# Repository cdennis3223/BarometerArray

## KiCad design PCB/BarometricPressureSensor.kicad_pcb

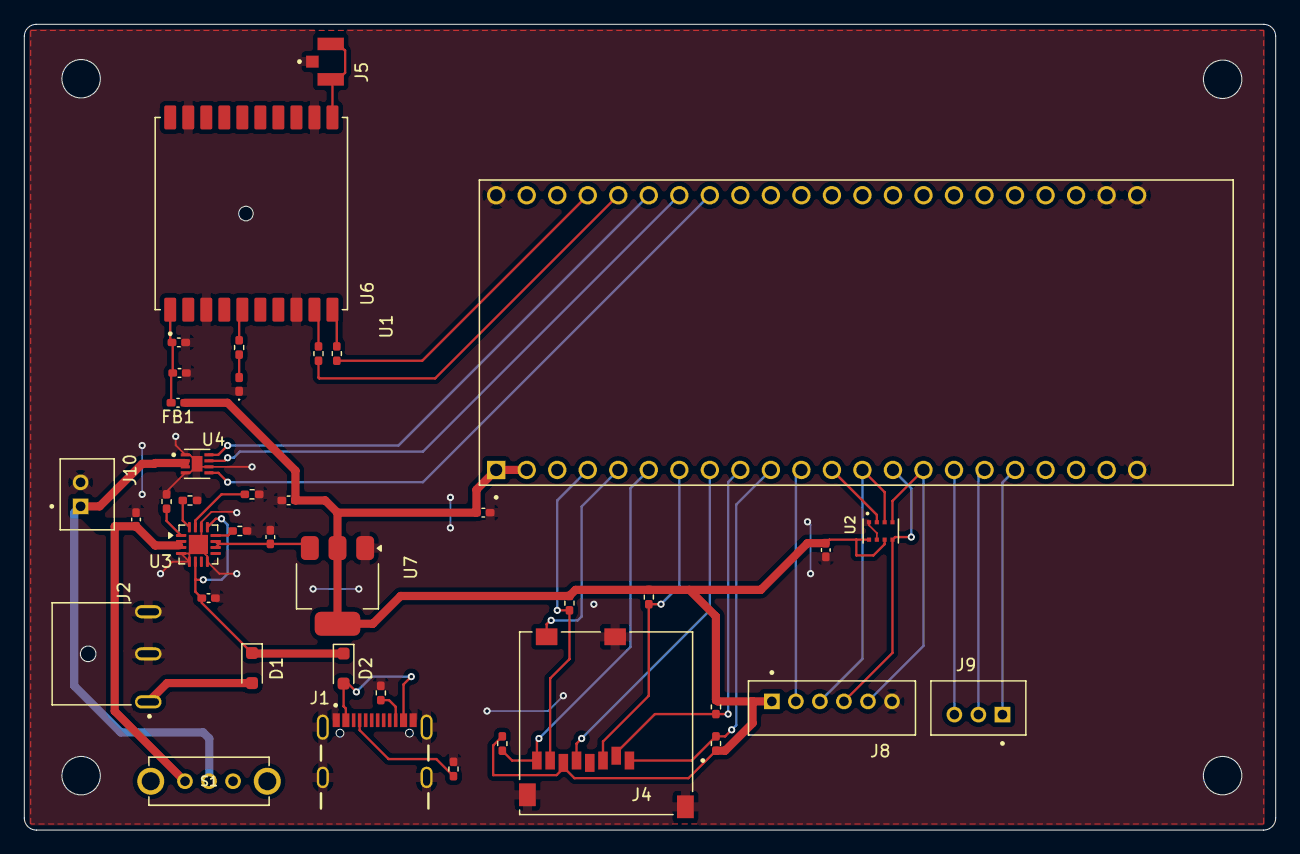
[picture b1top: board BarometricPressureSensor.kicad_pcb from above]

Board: 2 copper layers, 104.1 x 67.1 mm, 40 parts (0 on the bottom side), 39 nets.

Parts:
C1, C3: 100nF; C_0402_1005Metric_Pad0.74x0.62mm_HandSolder
C2, C8: 10uF; C_0402_1005Metric_Pad0.74x0.62mm_HandSolder
C4, C7: 1uF; C_0402_1005Metric_Pad0.74x0.62mm_HandSolder
C5: 0.1uF; C_0402_1005Metric_Pad0.74x0.62mm_HandSolder
C6: 4.7uF; C_0402_1005Metric_Pad0.74x0.62mm_HandSolder
D1, D2: D_Schottky; D_SOD-323_HandSoldering
D3: LED; LED_0402_1005Metric_Pad0.77x0.64mm_HandSolder
FB1: FerriteBead_Small; L_0402_1005Metric_Pad0.77x0.64mm_HandSolder
J1: USB4105-GF-A; GCT_USB4105-GF-A
J2: 54-00125; TENSILITY_54-00125
J4: GTFP08441BEU; AMPHENOL_GTFP08441BEU
J5: 2337019-1; TE_2337019-1
J8: B6B-PH-K-S; JST_B6B-PH-K-S
J9: B3B-PH-K-S; JST_B3B-PH-K-S
J10: B2B-PH-K-S; JST_B2B-PH-K-S
R1, R2: 5.1k; R_0402_1005Metric_Pad0.72x0.64mm_HandSolder
R3, R7, R8, R9, R10, R11: 10k; R_0402_1005Metric_Pad0.72x0.64mm_HandSolder
R4, R6: 3k; R_0402_1005Metric_Pad0.72x0.64mm_HandSolder
R5: 300; R_0402_1005Metric_Pad0.72x0.64mm_HandSolder
R12, R13, R14: 470; R_0402_1005Metric_Pad0.72x0.64mm_HandSolder
S1: EG1213; SW_EG1213
U1: ESP32-S3-DEVKITC-1-N16R8V; XCVR_ESP32-S3-DEVKITC-1-N16R8V
U2: DPS368XTSA1; XDCR_DPS368XTSA1
U3: BQ24074RGT; VQFN-16-1EP_3x3mm_P0.5mm_EP1.6x1.6mm
U4: MAX17048G_T10; SON50P200X200X80-9N
U6: CD-PA1616D; XCVR_CD-PA1616D
U7: LD1117S33TR_SOT223; SOT-223-3_TabPin2

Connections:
+3V3: C2.1, C3.2, C8.1, FB1.1, J4.6 (VSS), J8.1, R7.1, R8.1, R9.1, R10.2, R11.2, U1.J1_1 (3V3), U1.J1_2 (3V3), U2.6 (VDDIO), U2.8 (VDD), U7.2 (VO)
+BATT: C6.1, J10.1, S1.1, S1.2, U3.2 (BAT), U3.3 (BAT), U4.2 (CELL), U4.3 (VDD)
/CMD: J4.3 (CMD), R7.2, U1.J1_7 (GPIO7)
/CS1: U1.J1_12 (GPIO8), U2.2 (CSB)
/CS2: J8.2, U1.J1_11 (GPIO18)
/D0: J4.7 (DAT0), R11.1, U1.J1_4 (GPIO4)
/D1: J4.8 (DAT1), R10.1, U1.J1_6 (GPIO6)
/D2: J4.1 (DAT2), R8.2, U1.J1_10 (GPIO17)
/D3: J4.2 (CD/DAT3), R9.2, U1.J1_9 (GPIO16)
/DPSCLK: J8.5, U1.J1_15 (GPIO9), U2.4 (SCK)
/DPSMISO: J8.4, U1.J1_14 (GPIO46), U2.5 (SDO)
/DPSMOSI: J8.3, U1.J1_13 (GPIO3), U2.3 (SDI)
/GPSRX: R13.1, U1.J3_5 (GPIO2)
/GPSTX: R14.1, U1.J3_4 (GPIO1)
/IN: C7.1, D1.1 (K), D2.1 (K), U3.6 (EN1), U3.13 (IN)
/MAXALRT: U1.J3_8 (MTDO/GPIO40), U4.5 (~ALERT)
/MAXSCL: U1.J3_7 (MTDI/GPIO41), U4.7 (SCL)
/MAXSDA: U1.J3_6 (MTMS/GPIO42), U4.8 (SDA)
/OLEDBUT: J9.3, U1.J1_16 (GPIO10)
/OLEDSCL: J9.2, U1.J1_17 (GPIO11)
/OLEDSDA: J9.1, U1.J1_18 (GPIO12)
/SDCLK: J4.5 (CLK), U1.J1_8 (GPIO15)
/SDDET: J4.CD_PIN, U1.J1_5 (GPIO5)
GND: C1.2, C2.2, C3.1, C4.2, C5.2, C6.2, C7.2, C8.2, D3.1 (K), J1.A1_B12 (GND), J1.B1_A12 (GND__1), J1.SH1 (SHELL_GND), J1.SH2 (SHELL_GND__1), J1.SH3 (SHELL_GND__2), J1.SH4 (SHELL_GND__3), J2.B, J2.C, J4.G1 (SHIELD_GND), J4.G2 (SHIELD_GND__1), J4.G3 (SHIELD_GND__2), J5.1, J8.6, J10.2, R1.2, R2.2, R3.2, R4.1, R5.1, R6.1, U1.J1_22 (GND), U1.J3_1 (GND), U1.J3_21 (GND), U1.J3_22 (GND), U2.1 (GND), U2.7 (GND), U3.4 (~CE), U3.5 (EN2), U3.8 (VSS), U3.14 (TMR), U3.17 (VSS), U4.1 (CTG), U4.4 (GND), U4.6 (QSTRT), U4.9 (EP), U6.3 (GND), U6.8 (GND), U6.12 (GND), U6.19 (GND), U7.1 (GND)
unnamed: D1.2 (A), J2.A
unnamed: D2.2 (A), J1.A4_B9 (VBUS), J1.B4_A9 (VBUS__1)
unnamed: D3.2 (A), R12.2
unnamed: J1.A5 (CC1), R1.1
unnamed: J1.B5 (CC2), R2.1
unnamed: R6.2, U3.12 (ILIM)
unnamed: R4.2, U3.16 (ISET)
unnamed: R5.2, U3.15 (ITERM)
unnamed: R3.1, U3.1 (TS)
unnamed: R12.1, U6.5 (3D-FIX)
unnamed: J5.G1, J5.G2, U6.11 (EX_ANT)
unnamed: R14.2, U6.10 (RX)
unnamed: R13.2, U6.9 (TX)
unnamed: C4.1, C5.1, FB1.2, U6.1 (VCC)
unnamed: C1.1, U3.10 (OUT), U3.11 (OUT), U7.3 (VI)

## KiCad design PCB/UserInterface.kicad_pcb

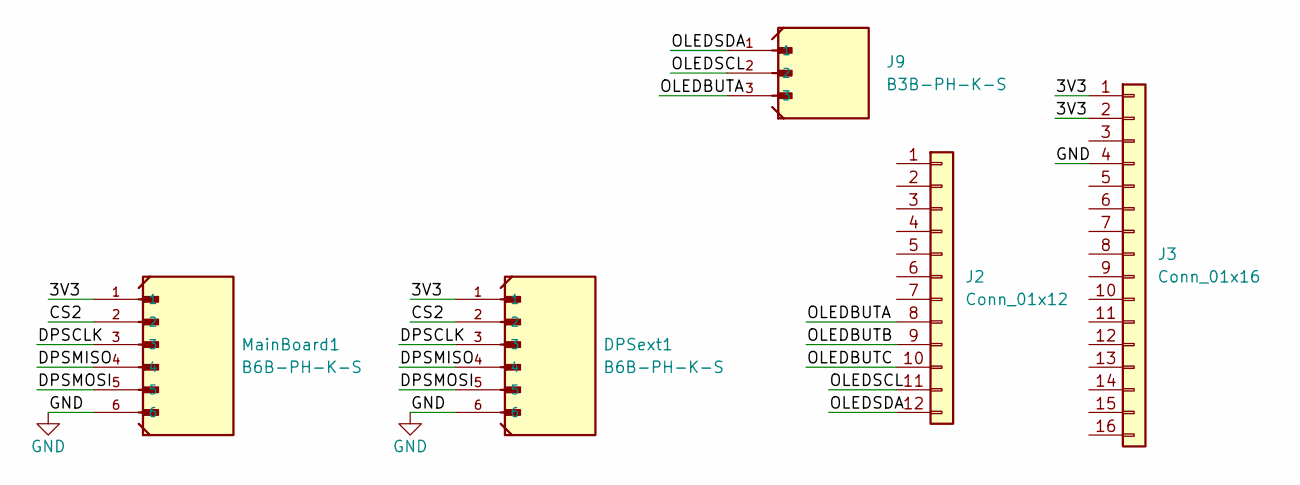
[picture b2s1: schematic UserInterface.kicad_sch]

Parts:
DPSext1: B6B-PH-K-S; JST_B6B-PH-K-S
J2: Conn_01x12; PinSocket_1x12_P2.54mm_Vertical
J3: Conn_01x16; PinSocket_1x16_P2.54mm_Vertical
J9: B3B-PH-K-S; JST_B3B-PH-K-S
MainBoard1: B6B-PH-K-S; JST_B6B-PH-K-S

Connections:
/3V3: DPSext1.1, J3.1, J3.2, MainBoard1.1
/CS2: DPSext1.2, MainBoard1.2
/DPSCLK: DPSext1.3, MainBoard1.3
/DPSMISO: DPSext1.4, MainBoard1.4
/DPSMOSI: DPSext1.5, MainBoard1.5
/OLEDBUTA: J2.8, J9.3
/OLEDBUTB: J2.9
/OLEDBUTC: J2.10
/OLEDSCL: J2.11, J9.2
/OLEDSDA: J2.12, J9.1
GND: DPSext1.6, J3.4, MainBoard1.6

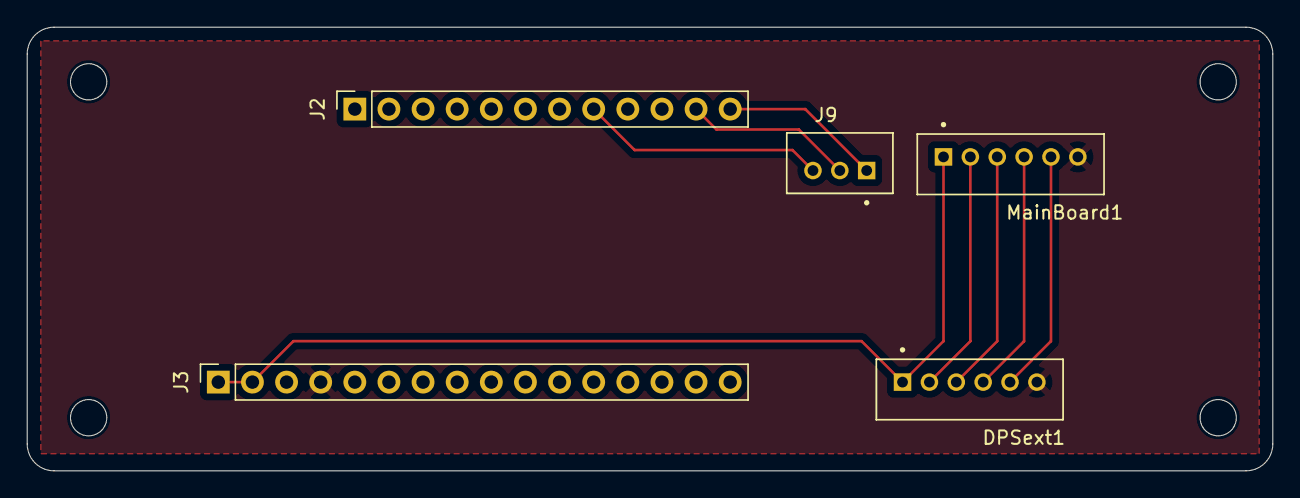
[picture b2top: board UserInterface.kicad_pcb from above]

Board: 2 copper layers, 92.7 x 33.0 mm, 5 parts (0 on the bottom side), 9 nets.

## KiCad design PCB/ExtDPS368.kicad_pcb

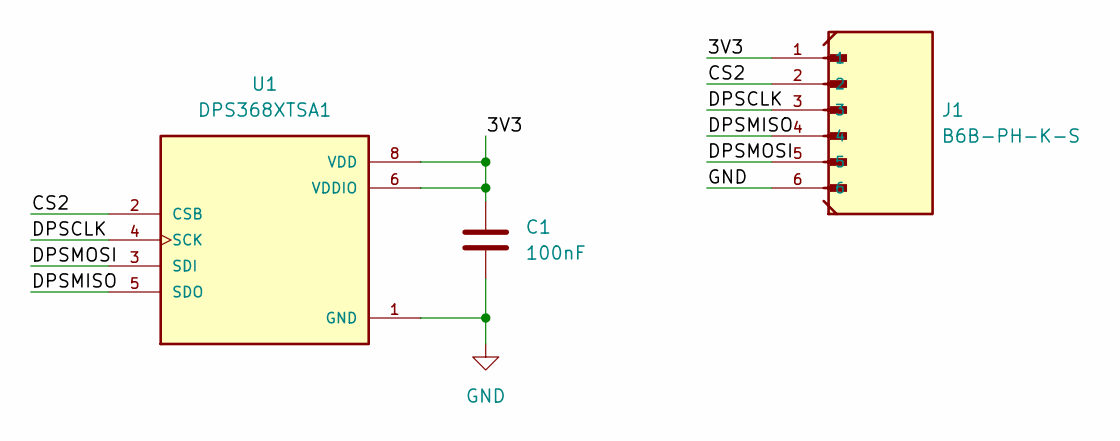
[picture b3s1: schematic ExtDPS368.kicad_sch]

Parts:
C1: 100nF; C_0402_1005Metric_Pad0.74x0.62mm_HandSolder
J1: B6B-PH-K-S; JST_B6B-PH-K-S
U1: DPS368XTSA1; XDCR_DPS368XTSA1

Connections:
/3V3: C1.1, J1.1, U1.6 (VDDIO), U1.8 (VDD)
/CS2: J1.2, U1.2 (CSB)
/DPSCLK: J1.3, U1.4 (SCK)
/DPSMISO: J1.4, U1.5 (SDO)
/DPSMOSI: J1.5, U1.3 (SDI)
GND: C1.2, J1.6, U1.1 (GND), U1.7 (GND)

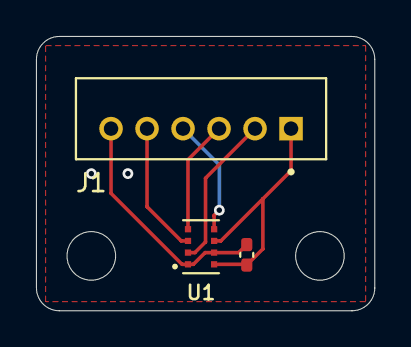
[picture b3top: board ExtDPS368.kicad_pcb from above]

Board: 2 copper layers, 18.8 x 15.2 mm, 3 parts (0 on the bottom side), 6 nets.

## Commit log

2026-02-02 attempting to push to Carl's repo
2026-02-02 Microcontroller communicates with GPS module.
2026-02-02 trying to push to Carls repo
2026-02-02 another attempt
2026-02-02 Hoping this goes through
2026-02-03 Moved files around
2026-02-03 Moved GPS code to separte source and header file. Code works
2026-02-04 My First Commit
2026-02-05 I think I have established communication with the pressure sensor. However I am just printing a serial number currently.
2026-02-09 The MISO and SCLK lines are working however the SDO of the DPS is not working. There seems to be a vague square wave but it is small and malformed
2026-02-09 this is old potentially working code
2026-02-11 Added Coefficient function and updated main to obtain them
2026-02-11 Fixed the Coefficient Values
2026-02-11 Updated Coefficients and corrected Temperature and pressure equations
2026-02-11 Currently Trying to debug Scaling issue with pressure and temperature output
2026-02-13 Working DPS Sensor, still finalizing initialization
2026-02-16 working Code for DPS Sensor, All initialization in the DPS.c file.
2026-02-18 Initial portions of SD.c and SD.h to start writing to the SD Card, Not tested Yet.
2026-02-27 clean code that prints horizontal!
2026-03-02 worked on encapsulating functions from main to DPS.c pressure sensor modules, good progress, code is cleaner still needs some work
2026-03-03 better organized the code for the pressure sensor module
2026-03-06 Reorganized repo: firmware files moved into firmware folder and added a PCB and mechanical folder
2026-03-06 new folders were not added to remote because they were empth, I fixed the issue by adding .gitkeep files within PCB and mechanical folders
2026-03-09 Working SD card code and untested BatMGMT code
2026-03-09 Fixing File errors
2026-03-11 Add files via upload
    Updated the switch we are using for the PCB. Will need to order these switches on our own.
2026-03-12 Add files via upload
    Updated Sizing on User Interface
2026-03-21 created a new collate module that implements a ring buffer to store timestamped measurements from the DPS368 pressure sensor before pushing it to the SD card. There is a task that runs in collate.c t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
2026-03-23 Updated BatMGMT.c and .h files with potentially working I2C, need to test still
2026-03-30 added 3D models for USB, SD Card module, and switch components of mainboard in PCB design
2026-03-30 saving all changes before merging
2026-03-30 added button functionality for cycling through screen readouts
2026-04-01 Add files via upload
    The current state of the container design, with a "Lid" That is in design still
2026-04-01 Added another component and renamed PCB.step, updated Lid to make container smoother
2026-04-03 Add files via upload
    Updated Container design and added the front cap to it.
2026-04-06 Added GPS timestamping to pressure sample ring buffer, program now timestamps samples and prints them to the serial, next steps are adding PPS synchronization and then saving to SD card
2026-04-08 Added all passthrough holes for user interface, and added mounting holes for PCB inside case and fixed front cap, might be ready to print a prototype.
2026-04-08 fixed errors in BatMGMT module that caused compiler to fail
2026-04-08 Updated .h files to match PCB
2026-04-08 Updated the platformio.ini file and fixed BatMGT.h error
2026-04-13 improved screen module code, moved screen.h from src to include folder
2026-04-13 tweaked the screen.c file to reflect final screen options better
2026-04-16 Working SD writes and Battery Management code
2026-04-16 Updated init for DPS to 32Hz for pressure and temp measurements
2026-04-17 Updated Logger task, main is currently in development
2026-04-17 Fixed BatMGMT.h
2026-04-17 logger fix
2026-04-17 collate fix
2026-04-17 should work
2026-04-17 logger problems
2026-04-17 test
2026-04-17 file movements
2026-04-17 Code will build
2026-04-17 Working code?
2026-04-17 added GPS viewing to UI
2026-04-19 Added functionaliity to UI, now can view GPS data(longitude, latitude, UTC) and Pressure Sensor Data(pressure and temp)
2026-04-19 Added a global watch file for shutdown tasks, added long and short button press on OLED screen and shutdown procedures for collate and logger tasks.
2026-04-19 added battery status to user interface display
2026-04-19 Final commit of the night, updated GPS with some potential PPS functionality, updated logger to have UTC time and ESP time columns and a valid column for GPS fix
2026-04-20 added SD status to user interface, fixed problem with GPS data not displaying on screen
2026-04-20 Improved logger.c file. Added SD card detection functionality. Can now handle unexpected removal and allow reinsertion
2026-04-20 added battery volage back to logging, added comments to logger.c, cleaned main.c
2026-04-22 Updated logger to log real time in YYYY MM DD MM SS.SSS and added more decimal places to pressure samples
2026-04-27 Add files via upload
    Updated PPS and SD Schematic
2026-04-27 Annotated main board schematic, corrected switch short on main PCB
2026-04-27 Add files via upload
    Container version 2!
2026-04-28 added more comments to code to improve documentation
2026-04-30 fixed bug with pressure not being displayed without SD inserted, improved user interface
2026-04-30 fixed overflow issue with millisecond field of sample_t struct
2026-05-01 added comments to the GPSparser file
2026-05-01 added comments to GPS code
2026-05-02 fixed issue with millisecond NMEA timestamp, added some comments
2026-05-02 fixed PPS synchronization issues, PPS sync appears to work without any issue now
2026-05-02 fixed PPS and NMEA timing coordination problem, viewed log csv files, looks fixed now, made other small improvements to code
2026-05-05 broke main board schematic into smaller schematics, annotated and organized
2026-05-08 implemented external dps sensor
2026-05-08 Updated Screen to show both pressure and temperature measurements
